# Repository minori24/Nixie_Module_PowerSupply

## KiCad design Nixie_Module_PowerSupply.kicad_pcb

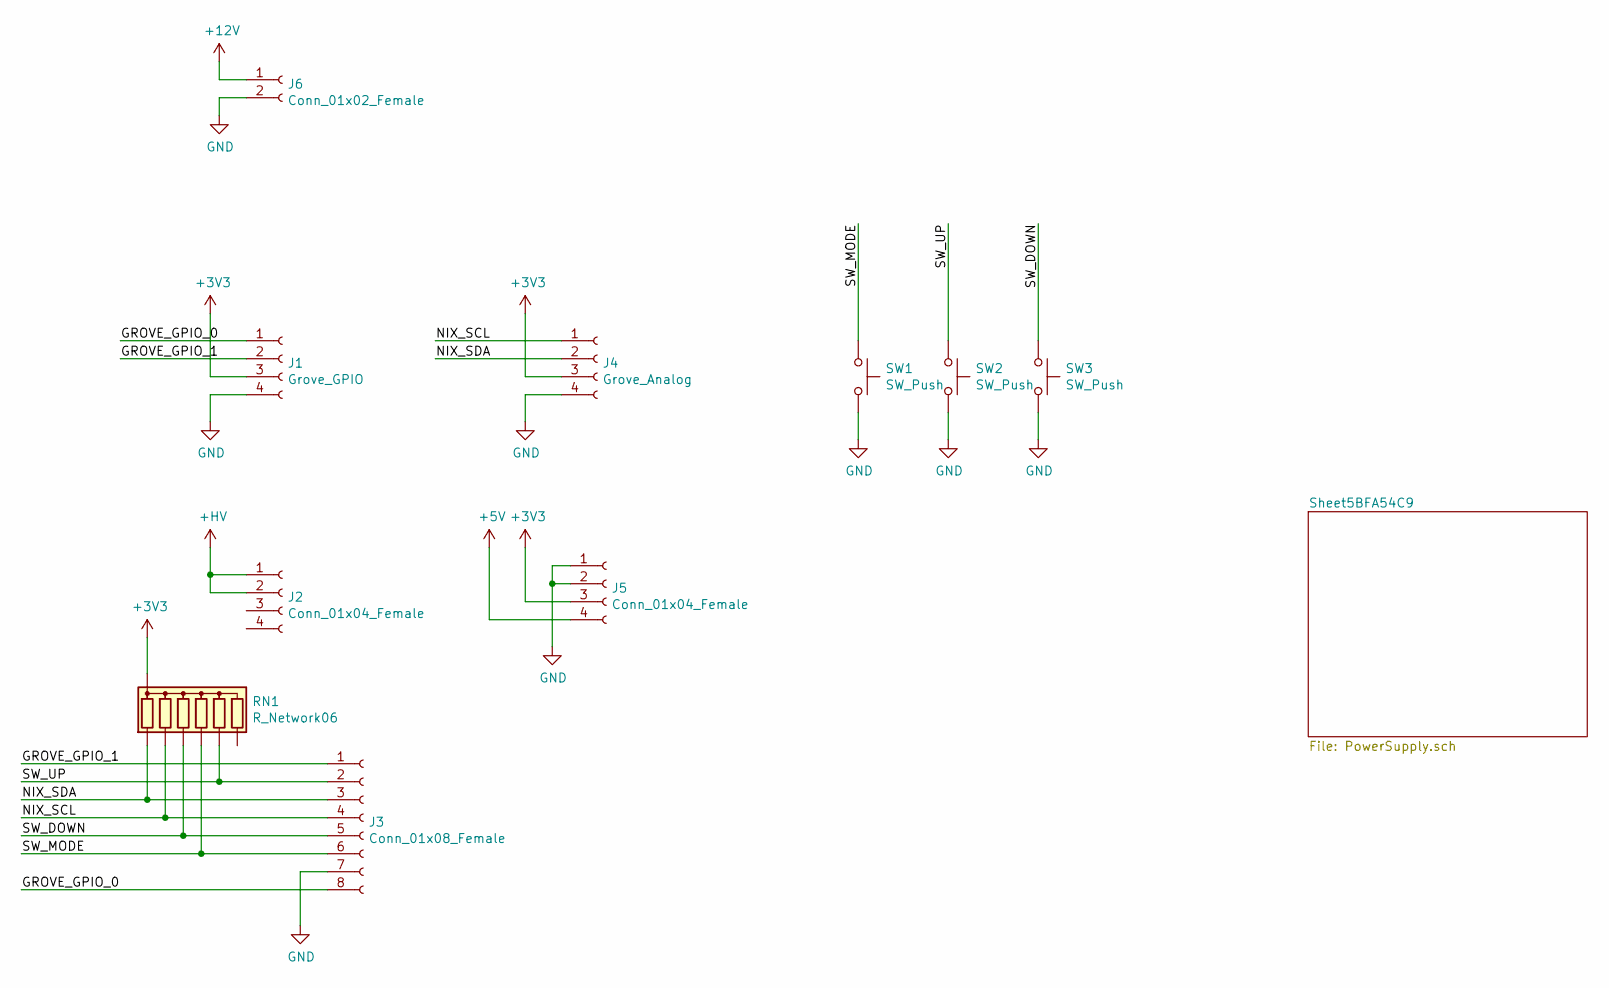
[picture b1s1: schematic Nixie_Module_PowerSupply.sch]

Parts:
J1: Grove_GPIO; Grove_THT
J2, J5: Conn_01x04_Female; PinSocket_2x02_P2.54mm_Vertical
J3: Conn_01x08_Female; PinSocket_2x04_P2.54mm_Vertical
J4: Grove_Analog; Grove_THT
J6: Conn_01x02_Female; JST_XH_S02B-XH-A_02x2.50mm_Angled
RN1: R_Network06; R_Array_SIP7
SW1, SW2, SW3: SW_Push; SW_Tactile_SPST_Angled_PTS645Vx31-2LFS

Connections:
+3V3: J1.3, J4.3, J5.3, RN1.1 (common); also elsewhere on the board
+5V: J5.4; also elsewhere on the board
+12V: J6.1; also elsewhere on the board
+HV: J2.1, J2.2; also elsewhere on the board
/GROVE_GPIO_0: J1.1, J3.8
/GROVE_GPIO_1: J1.2, J3.1
/NIX_SCL: J3.4, J4.1, RN1.3 (R2)
/NIX_SDA: J3.3, J4.2, RN1.2 (R1)
/SW_DOWN: J3.5, RN1.4 (R3), SW3.1
/SW_MODE: J3.6, RN1.5 (R4), SW1.1
/SW_UP: J3.2, RN1.6 (R5), SW2.1
GND: J1.4, J3.7, J4.4, J5.1, J5.2, J6.2, SW1.2, SW2.2, SW3.2; also elsewhere on the board

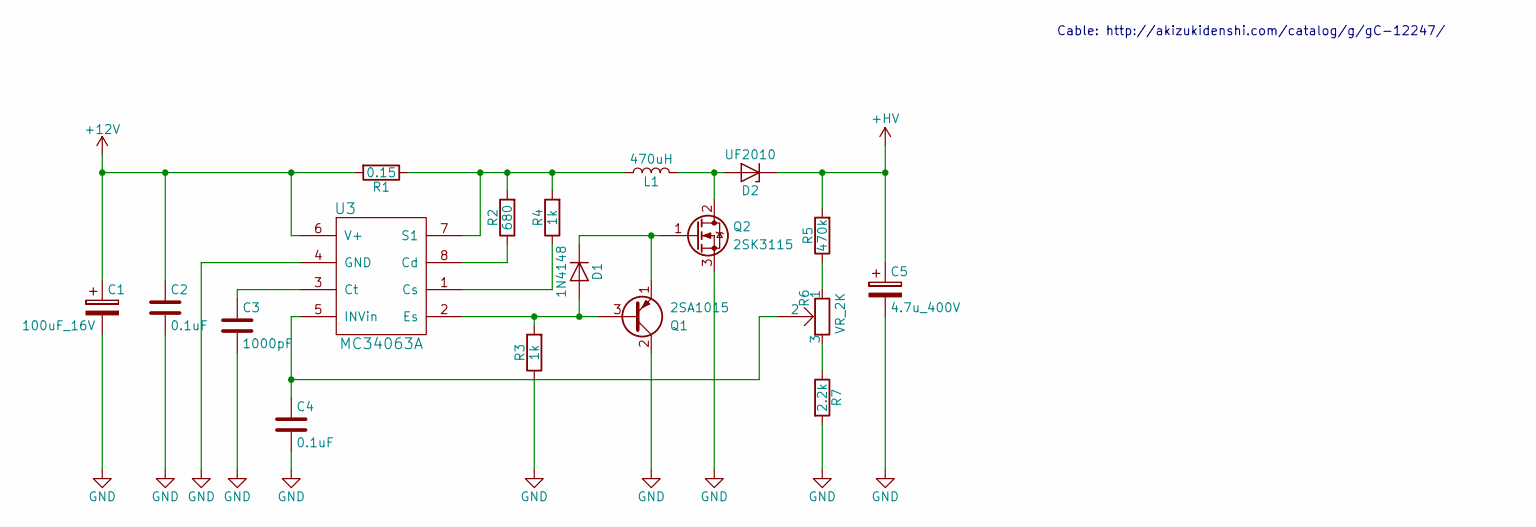
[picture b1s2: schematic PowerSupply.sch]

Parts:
C1: 100uF_16V; CP_Radial_D6.3mm_P2.50mm
C2, C4: 0.1uF; C_Disc_D5.0mm_W2.5mm_P5.00mm
C3: 1000pF; C_Disc_D5.0mm_W2.5mm_P5.00mm
C5: 4.7u_400V; CP_Radial_D10.0mm_P5.00mm
D1: 1N4148; D_DO-35_SOD27_P7.62mm_Horizontal
D2: UF2010; D_DO-15_P10.16mm_Horizontal
L1: 470uH; Inductors_LHL13NB471K
Q1: 2SA1015; TO-92_Wide
Q2: 2SK3115; TO-220-3_Vertical
R1: 0.15; R_Axial_DIN0207_L6.3mm_D2.5mm_P7.62mm_Horizontal
R2: 680; R_Axial_DIN0207_L6.3mm_D2.5mm_P2.54mm_Vertical
R3: 1k; R_Axial_DIN0207_L6.3mm_D2.5mm_P7.62mm_Horizontal
R4: 1k; R_Axial_DIN0207_L6.3mm_D2.5mm_P2.54mm_Vertical
R5: 470k; R_Axial_DIN0207_L6.3mm_D2.5mm_P2.54mm_Vertical
R6: VR_2K; VOL_3362P-1-202LF
R7: 2.2k; R_Axial_DIN0207_L6.3mm_D2.5mm_P2.54mm_Vertical
U3: MC34063A; DIP-8_W7.62mm

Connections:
+12V: C1.1, C2.1, R1.2, U3.6 (V+); also elsewhere on the board
+HV: C5.1, D2.1 (K), R5.2; also elsewhere on the board
GND: C1.2, C2.2, C3.2, C4.2, C5.2, Q1.2 (C), Q2.3 (S), R3.1, R7.2, U3.4 (GND); also elsewhere on the board
unnamed: C3.1, U3.3 (Ct)
unnamed: C4.1, R6.2, U3.5 (INVin)
unnamed: D1.1 (K), Q1.1 (E), Q2.1 (G)
unnamed: D1.2 (A), Q1.3 (B), R3.2, U3.2 (Es)
unnamed: D2.2 (A), L1.2, Q2.2 (D)
unnamed: L1.1, R1.1, R2.2, R4.2, U3.7 (S1)
unnamed: R2.1, U3.8 (Cd)
unnamed: R4.1, U3.1 (Cs)
unnamed: R5.1, R6.1
unnamed: R6.3, R7.1

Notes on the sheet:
Cable: http://akizukidenshi.com/catalog/g/gC-12247/

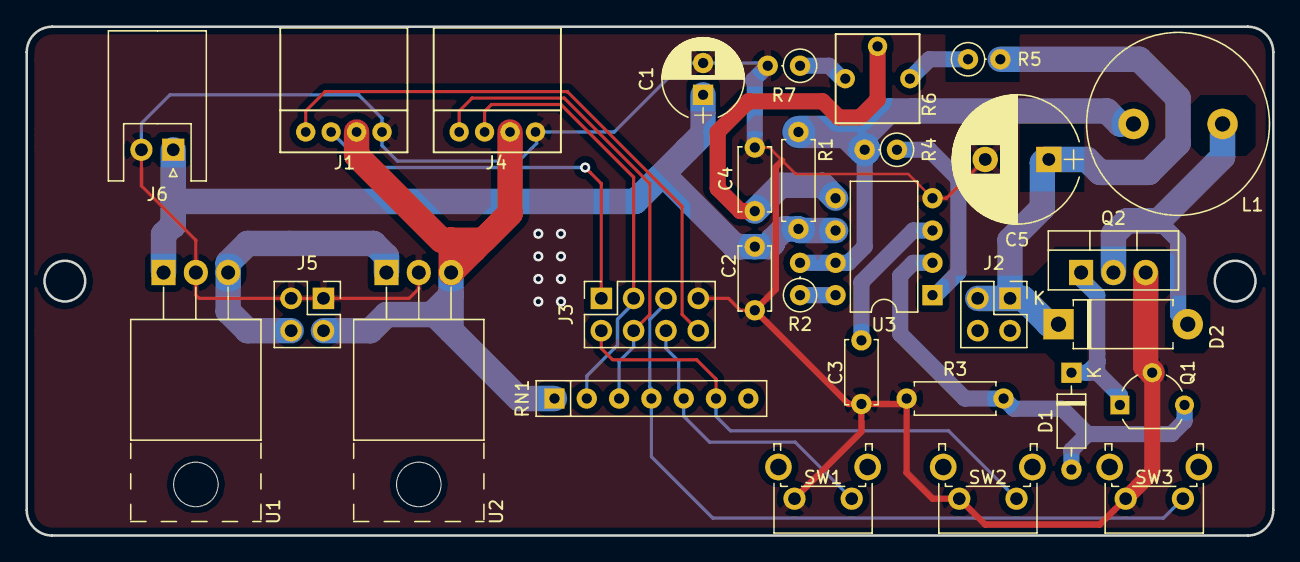
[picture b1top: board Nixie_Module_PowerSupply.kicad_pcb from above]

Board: 2 copper layers, 98.0 x 40.0 mm, 30 parts (0 on the bottom side), 22 nets.

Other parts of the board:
U1, U2: NJM7805S; TO-220-3_Horizontal_TabUp

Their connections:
+3V3: U2.3; also elsewhere on the board
+5V: U1.3, U2.1; also elsewhere on the board
+12V: U1.1; also elsewhere on the board
GND: U1.2, U2.2; also elsewhere on the board
